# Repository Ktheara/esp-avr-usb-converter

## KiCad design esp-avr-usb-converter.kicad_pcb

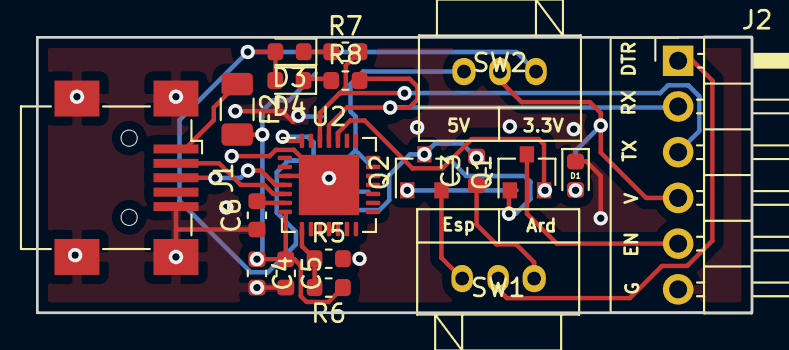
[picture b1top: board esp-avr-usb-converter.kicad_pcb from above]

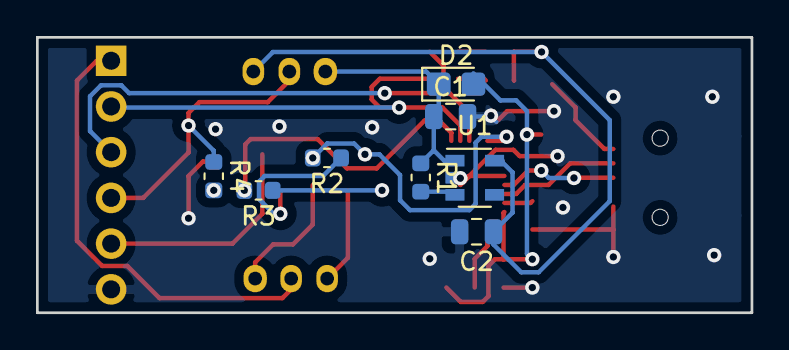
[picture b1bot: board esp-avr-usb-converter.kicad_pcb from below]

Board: 2 copper layers, 39.7 x 15.3 mm, 27 parts (8 on the bottom side), 24 nets.

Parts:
C1, C2: 10u; C_0805_2012Metric
C3, C4, C6: 100n; C_0603_1608Metric
C5: 1u; C_0603_1608Metric
D1: R; LED_0603_1608Metric
D2: 1N5819WS; D_0805_2012Metric_Castellated
D3, D4: B; LED_0603_1608Metric
F2: 500mA; Fuse_1206_3216Metric
J1: USB_B_Mini; USB_Mini-B_Wuerth_65100516121_Horizontal
J2: Conn_01x06; PinHeader_1x06_P2.54mm_Horizontal
Q1, Q2: BSS138; SOT-23
R1, R2, R3: 10k; R_0603_1608Metric
R4, R7, R8: 1k; R_0603_1608Metric
R5: 47.5k; R_0603_1608Metric
R6: 22.1k; R_0603_1608Metric
SW1: Mode; SW-3P-SK12D07VG
SW2: 3.3V/5V; SW-3P-SK12D07VG
U1: SPX3819M5-L-3-3; SOT-23-5
U2: CP2102N-A01-GQFN28; QFN-28-1EP_5x5mm_P0.5mm_EP3.35x3.35mm

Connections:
+3V3: C2.1, D3.2, D4.2, SW2.1, U1.5
/CP2102N-GQFN28/5V: C1.1, D2.1, R1.1, SW2.3, U1.1
/CP2102N-GQFN28/D+: J1.3, U2.4
/CP2102N-GQFN28/D-: J1.2, U2.5
/CP2102N-GQFN28/DTR: C3.2, Q2.3, R2.2, U2.28
/CP2102N-GQFN28/RST: Q1.2, R3.2, U2.24
/CP2102N-GQFN28/VBUS: F2.1, J1.1
/CP2102N-GQFN28/VDD: C6.2, U2.6
/DTR: J2.1, SW1.2
/EN: J2.5, Q1.3
/RX: J2.2, R8.2, U2.25
/TX: J2.3, R7.2, U2.26
/VCC: J2.4, R4.1, SW2.2
GND: C1.2, C2.2, C4.2, C5.2, C6.1, D1.1, J1.5, J1.6, J2.6, R5.2, U1.2, U2.3, U2.29
unnamed: C3.1, SW1.3
unnamed: C4.1, C5.1, D2.2, F2.2, R6.1, U2.7
unnamed: D1.2, R4.2
unnamed: D3.1, R7.1
unnamed: D4.1, R8.1
unnamed: Q1.1, R2.1
unnamed: Q2.1, R3.1
unnamed: Q2.2, SW1.1
unnamed: R1.2, U1.3
unnamed: R5.1, R6.2, U2.8

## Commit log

2021-04-28 added files
